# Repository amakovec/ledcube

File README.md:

# blinky++ - An LED cube with some neat features

## Status

**This project has not yet been tested.  Boards are on their way and bring-up FW writing is in-progress.**

## Features

* Multiplex layers at >=120 Hz to create a persistence-of-vision effect
* USB-C for power and communications (except flashing)
    * Set current limit based on CC1 and CC2 voltage (not USB PD)
* Headers to allow for removal of the LED cube
* 30mA per LED
* Buttons to change displayed LED patterns
* Adjustable brightness
    * Limit brightness based on USB current limit determined above

## Hardware

* 2-layer board
* Less than 100x100mm (most budget PCB fabs have a significant price jump for dimensions larger than this)
* SAMD21-based

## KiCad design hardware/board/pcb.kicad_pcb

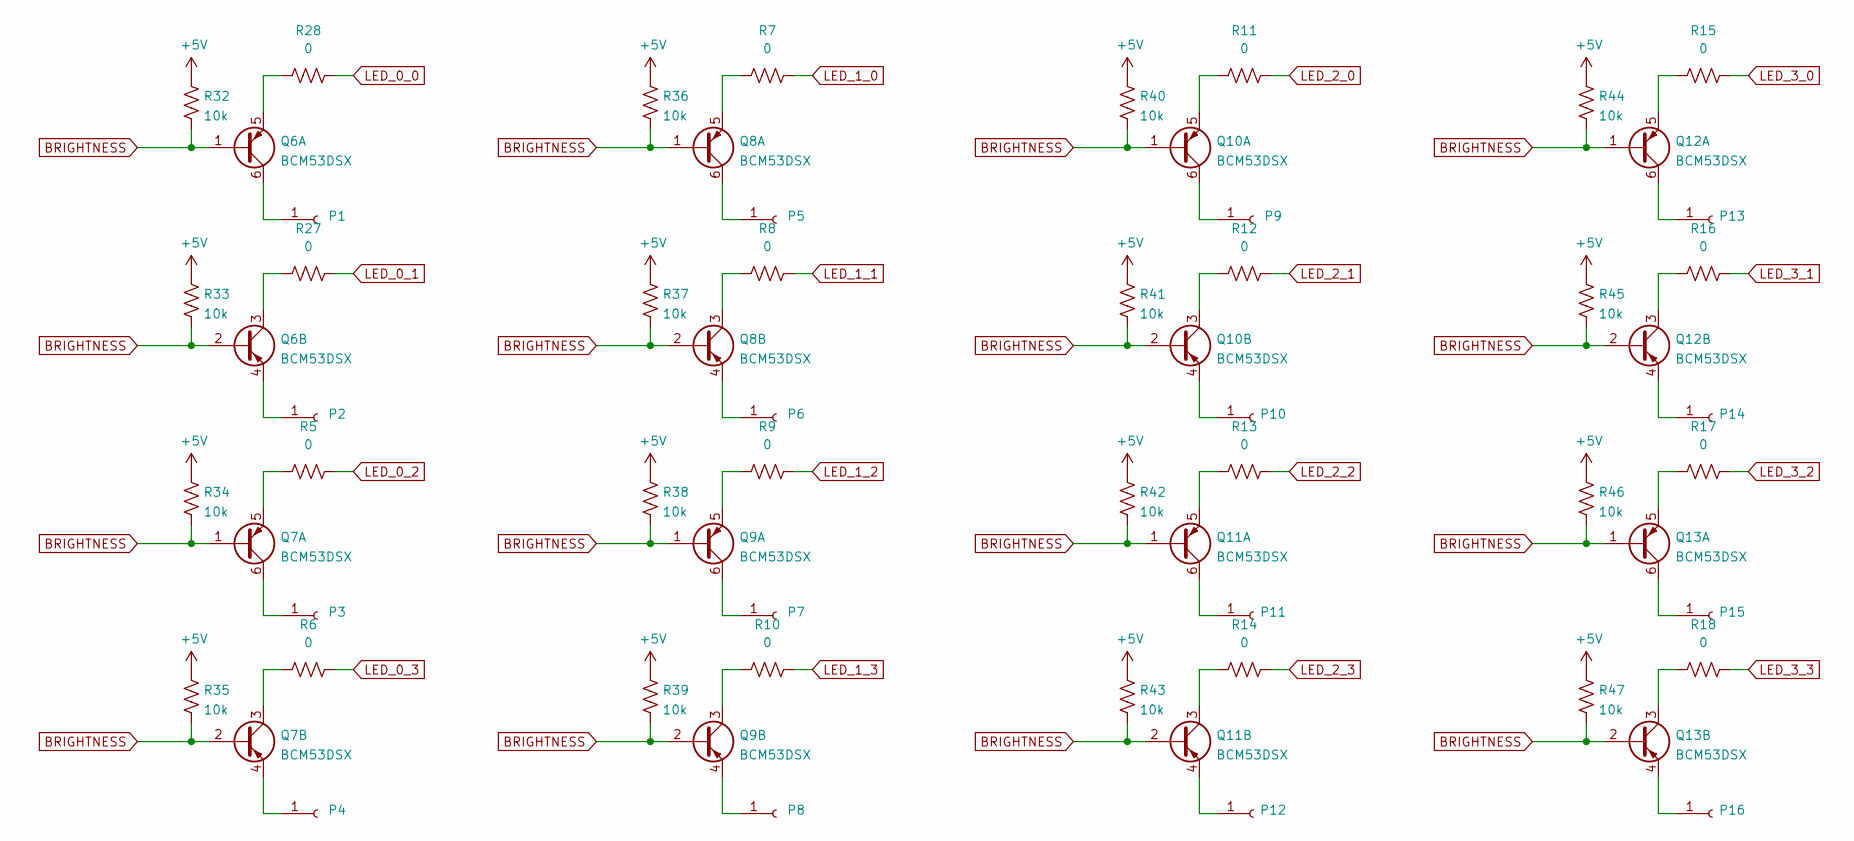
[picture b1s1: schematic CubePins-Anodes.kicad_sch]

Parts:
P1, P2, P3, P4, P5, P6, P7, P8, P9, P10, P11, P12, P13, P14, P15, P16: SSW-101-01-T-S
Q6, Q7, Q8, Q9, Q10, Q11, Q12, Q13: BCM53DSX; SC-74-6_1.5x2.9mm_P0.95mm
R5, R6, R7, R8, R9, R10, R11, R12, R13, R14, R15, R16, R17, R18, R27, R28: RC0402JR-070RP; R_0402_1005Metric_Pad0.72x0.64mm_HandSolder
R32, R33, R34, R35, R36, R37, R38, R39, R40, R41, R42, R43, R44, R45, R46, R47: RC0402FR-0710KL; R_0402_1005Metric_Pad0.72x0.64mm_HandSolder; Tolerance 1%

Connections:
+5V: R32.1, R33.1, R34.1, R35.1, R36.1, R37.1, R38.1, R39.1, R40.1, R41.1, R42.1, R43.1, R44.1, R45.1, R46.1, R47.1; also elsewhere on the board
BRIGHTNESS: Q6.1 (B2), Q6.2 (B2), Q7.1 (B2), Q7.2 (B2), Q8.1 (B2), Q8.2 (B2), Q9.1 (B2), Q9.2 (B2), Q10.1 (B2), Q10.2 (B2), Q11.1 (B2), Q11.2 (B2), Q12.1 (B2), Q12.2 (B2), Q13.1 (B2), Q13.2 (B2), R32.2, R33.2, R34.2, R35.2, R36.2, R37.2, R38.2, R39.2, R40.2, R41.2, R42.2, R43.2, R44.2, R45.2, R46.2, R47.2; also elsewhere on the board
LED_0_0: R28.1; also elsewhere on the board
LED_0_1: R27.1; also elsewhere on the board
LED_0_2: R5.1; also elsewhere on the board
LED_0_3: R6.1; also elsewhere on the board
LED_1_0: R7.1; also elsewhere on the board
LED_1_1: R8.1; also elsewhere on the board
LED_1_2: R9.1; also elsewhere on the board
LED_1_3: R10.1; also elsewhere on the board
LED_2_0: R11.1; also elsewhere on the board
LED_2_1: R12.1; also elsewhere on the board
LED_2_2: R13.1; also elsewhere on the board
LED_2_3: R14.1; also elsewhere on the board
LED_3_0: R15.1; also elsewhere on the board
LED_3_1: R16.1; also elsewhere on the board
LED_3_2: R17.1; also elsewhere on the board
LED_3_3: R18.1; also elsewhere on the board
unnamed: P1.1, Q6.6 (C2)
unnamed: P2.1, Q6.4 (E2)
unnamed: P3.1, Q7.6 (C2)
unnamed: P4.1, Q7.4 (E2)
unnamed: P5.1, Q8.6 (C2)
unnamed: P6.1, Q8.4 (E2)
unnamed: P7.1, Q9.6 (C2)
unnamed: P8.1, Q9.4 (E2)
unnamed: P9.1, Q10.6 (C2)
unnamed: P10.1, Q10.4 (E2)
unnamed: P11.1, Q11.6 (C2)
unnamed: P12.1, Q11.4 (E2)
unnamed: P13.1, Q12.6 (C2)
unnamed: P14.1, Q12.4 (E2)
unnamed: P15.1, Q13.6 (C2)
unnamed: P16.1, Q13.4 (E2)
unnamed: Q6.3 (C2), R27.2
unnamed: Q6.5 (E2), R28.2
unnamed: Q7.3 (C2), R6.2
unnamed: Q7.5 (E2), R5.2
unnamed: Q8.3 (C2), R8.2
unnamed: Q8.5 (E2), R7.2
unnamed: Q9.3 (C2), R10.2
unnamed: Q9.5 (E2), R9.2
unnamed: Q10.3 (C2), R12.2
unnamed: Q10.5 (E2), R11.2
unnamed: Q11.3 (C2), R14.2
unnamed: Q11.5 (E2), R13.2
unnamed: Q12.3 (C2), R16.2
unnamed: Q12.5 (E2), R15.2
unnamed: Q13.3 (C2), R18.2
unnamed: Q13.5 (E2), R17.2

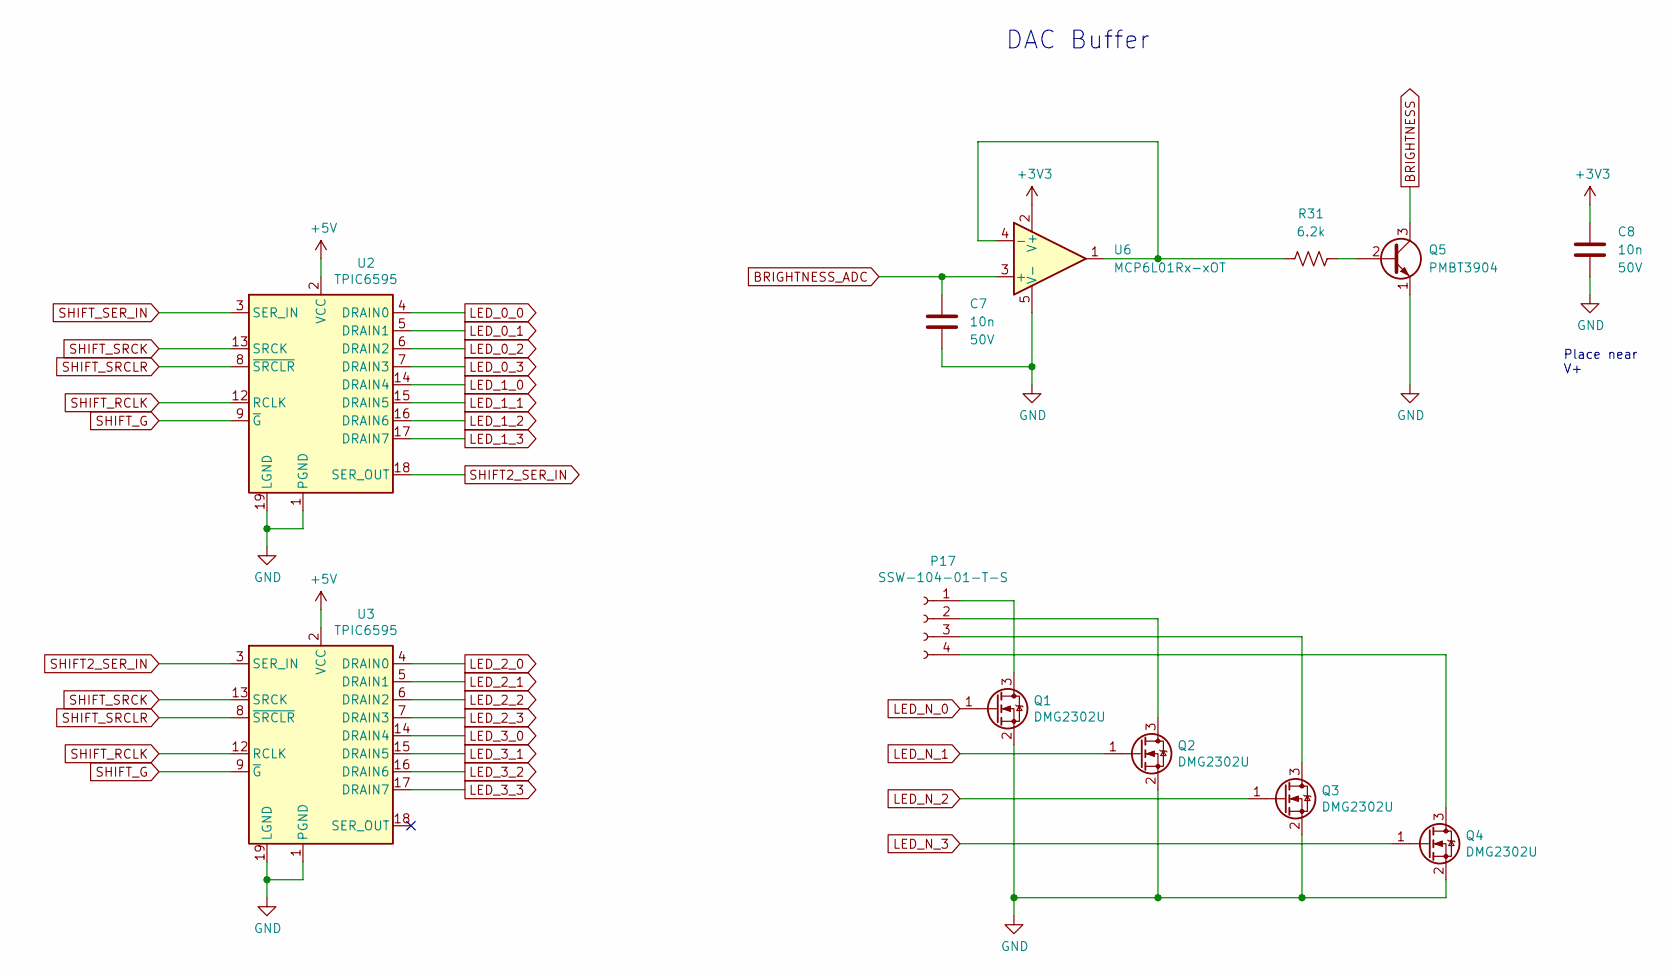
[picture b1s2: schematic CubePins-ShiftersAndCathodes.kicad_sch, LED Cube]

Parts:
C7, C8: GCM155R71H103KA55D; C_0402_1005Metric_Pad0.74x0.62mm_HandSolder; Voltage 50V; Rating X7R
P17: SSW-104-01-T-S
Q1, Q2, Q3, Q4: DMG2302U; SOT-23
Q5: PMBT3904; SOT-23
R31: RC0402FR-076K2L; R_0402_1005Metric_Pad0.72x0.64mm_HandSolder; Tolerance 1%
U2, U3: TPIC6595; SOIC-20W_7.5x12.8mm_P1.27mm
U6: MCP6L01Rx-xOT; SOT-23-5

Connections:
+3V3: C8.1, U6.2 (V+); also elsewhere on the board
+5V: U2.2 (VCC), U3.2 (VCC); also elsewhere on the board
BRIGHTNESS: Q5.3 (C); also elsewhere on the board
BRIGHTNESS_ADC: C7.1, U6.3 (+); also elsewhere on the board
LED_0_0: U2.4 (DRAIN0); also elsewhere on the board
LED_0_1: U2.5 (DRAIN1); also elsewhere on the board
LED_0_2: U2.6 (DRAIN2); also elsewhere on the board
LED_0_3: U2.7 (DRAIN3); also elsewhere on the board
LED_1_0: U2.14 (DRAIN4); also elsewhere on the board
LED_1_1: U2.15 (DRAIN5); also elsewhere on the board
LED_1_2: U2.16 (DRAIN6); also elsewhere on the board
LED_1_3: U2.17 (DRAIN7); also elsewhere on the board
LED_2_0: U3.4 (DRAIN0); also elsewhere on the board
LED_2_1: U3.5 (DRAIN1); also elsewhere on the board
LED_2_2: U3.6 (DRAIN2); also elsewhere on the board
LED_2_3: U3.7 (DRAIN3); also elsewhere on the board
LED_3_0: U3.14 (DRAIN4); also elsewhere on the board
LED_3_1: U3.15 (DRAIN5); also elsewhere on the board
LED_3_2: U3.16 (DRAIN6); also elsewhere on the board
LED_3_3: U3.17 (DRAIN7); also elsewhere on the board
LED_N_0: Q1.1 (G); also elsewhere on the board
LED_N_1: Q2.1 (G); also elsewhere on the board
LED_N_2: Q3.1 (G); also elsewhere on the board
LED_N_3: Q4.1 (G); also elsewhere on the board
unnamed: P17.1, Q1.3 (D)
unnamed: P17.2, Q2.3 (D)
unnamed: P17.3, Q3.3 (D)
unnamed: P17.4, Q4.3 (D)
unnamed: Q5.2 (B), R31.2
unnamed: R31.1, U6.1, U6.4 (-)
SHIFT2_SER_IN: U2.18 (SER_OUT), U3.3 (SER_IN)
SHIFT_G: U2.9 (~G), U3.9 (~G); also elsewhere on the board
SHIFT_RCLK: U2.12 (RCLK), U3.12 (RCLK); also elsewhere on the board
SHIFT_SER_IN: U2.3 (SER_IN); also elsewhere on the board
SHIFT_SRCK: U2.13 (SRCK), U3.13 (SRCK); also elsewhere on the board
SHIFT_SRCLR: U2.8 (~SRCLR), U3.8 (~SRCLR); also elsewhere on the board

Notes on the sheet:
DAC Buffer
Place near V+

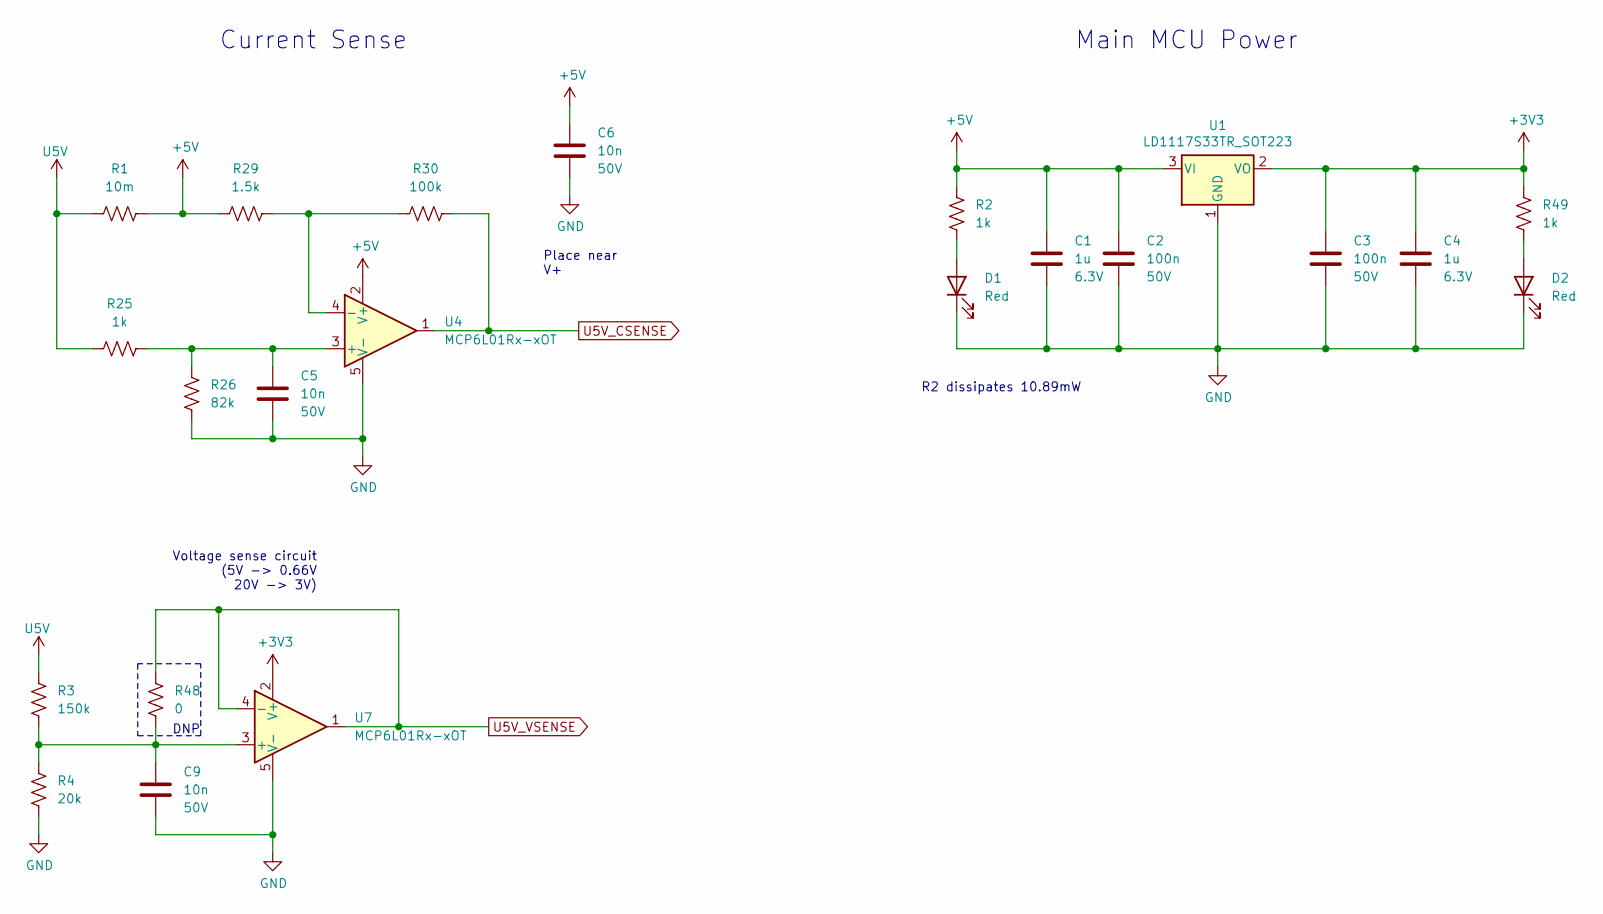
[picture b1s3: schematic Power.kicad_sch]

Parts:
C1, C4: CC0402KRX5R5BB105; C_0402_1005Metric_Pad0.74x0.62mm_HandSolder; Voltage 6.3V; Rating X5R
C2, C3: GRM155R71H104KE14D; C_0402_1005Metric_Pad0.74x0.62mm_HandSolder; Voltage 50V; Rating X7R
C5, C6, C9: GCM155R71H103KA55D; C_0402_1005Metric_Pad0.74x0.62mm_HandSolder; Voltage 50V; Rating X7R
D1, D2: 150060RS75000; LED_0603_1608Metric_Pad1.05x0.95mm_HandSolder
R1: CFG0612-FX-R010ELF; R_1206_3216Metric_Pad1.30x1.75mm_HandSolder; Tolerance 1%
R2, R49: RC0402JR-071KL; R_0402_1005Metric_Pad0.72x0.64mm_HandSolder
R3: RC0402FR-07150KL; R_0402_1005Metric_Pad0.72x0.64mm_HandSolder; Tolerance 1%
R4: RC0402FR-0720KL; R_0402_1005Metric_Pad0.72x0.64mm_HandSolder; Tolerance 1%
R25: RC0402FR-071KL; R_0402_1005Metric_Pad0.72x0.64mm_HandSolder; Tolerance 1%
R26: RC0402FR-0782KL; R_0402_1005Metric_Pad0.72x0.64mm_HandSolder; Tolerance 1%
R29: RC0402FR-071K5L; R_0402_1005Metric_Pad0.72x0.64mm_HandSolder; Tolerance 1%
R30: RC0402FR-07100KL; R_0402_1005Metric_Pad0.72x0.64mm_HandSolder; Tolerance 1%
R48: RC0402JR-070RP; R_0402_1005Metric_Pad0.72x0.64mm_HandSolder
U1: LD1117S33TR_SOT223; SOT-223-3_TabPin2
U4, U7: MCP6L01Rx-xOT; SOT-23-5

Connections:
+3V3: C3.1, C4.1, R49.1, U1.2 (VO), U7.2 (V+); also elsewhere on the board
+5V: C1.1, C2.1, C6.1, R1.2, R2.1, R29.1, U1.3 (VI), U4.2 (V+); also elsewhere on the board
unnamed: C5.1, R25.2, R26.1, U4.3 (+)
unnamed: C9.1, R3.2, R4.1, R48.1, U7.3 (+)
unnamed: D1.2 (A), R2.2
unnamed: D2.2 (A), R49.2
unnamed: R29.2, R30.1, U4.4 (-)
U5V: R1.1, R3.1, R25.1; also elsewhere on the board
U5V_CSENSE: R30.2, U4.1; also elsewhere on the board
U5V_VSENSE: R48.2, U7.1, U7.4 (-); also elsewhere on the board

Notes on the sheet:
DNP
Current Sense
Voltage sense circuit (5V -> 0.66V 20V -> 3V)
Place near V+
R2 dissipates 10.89mW
Main MCU Power

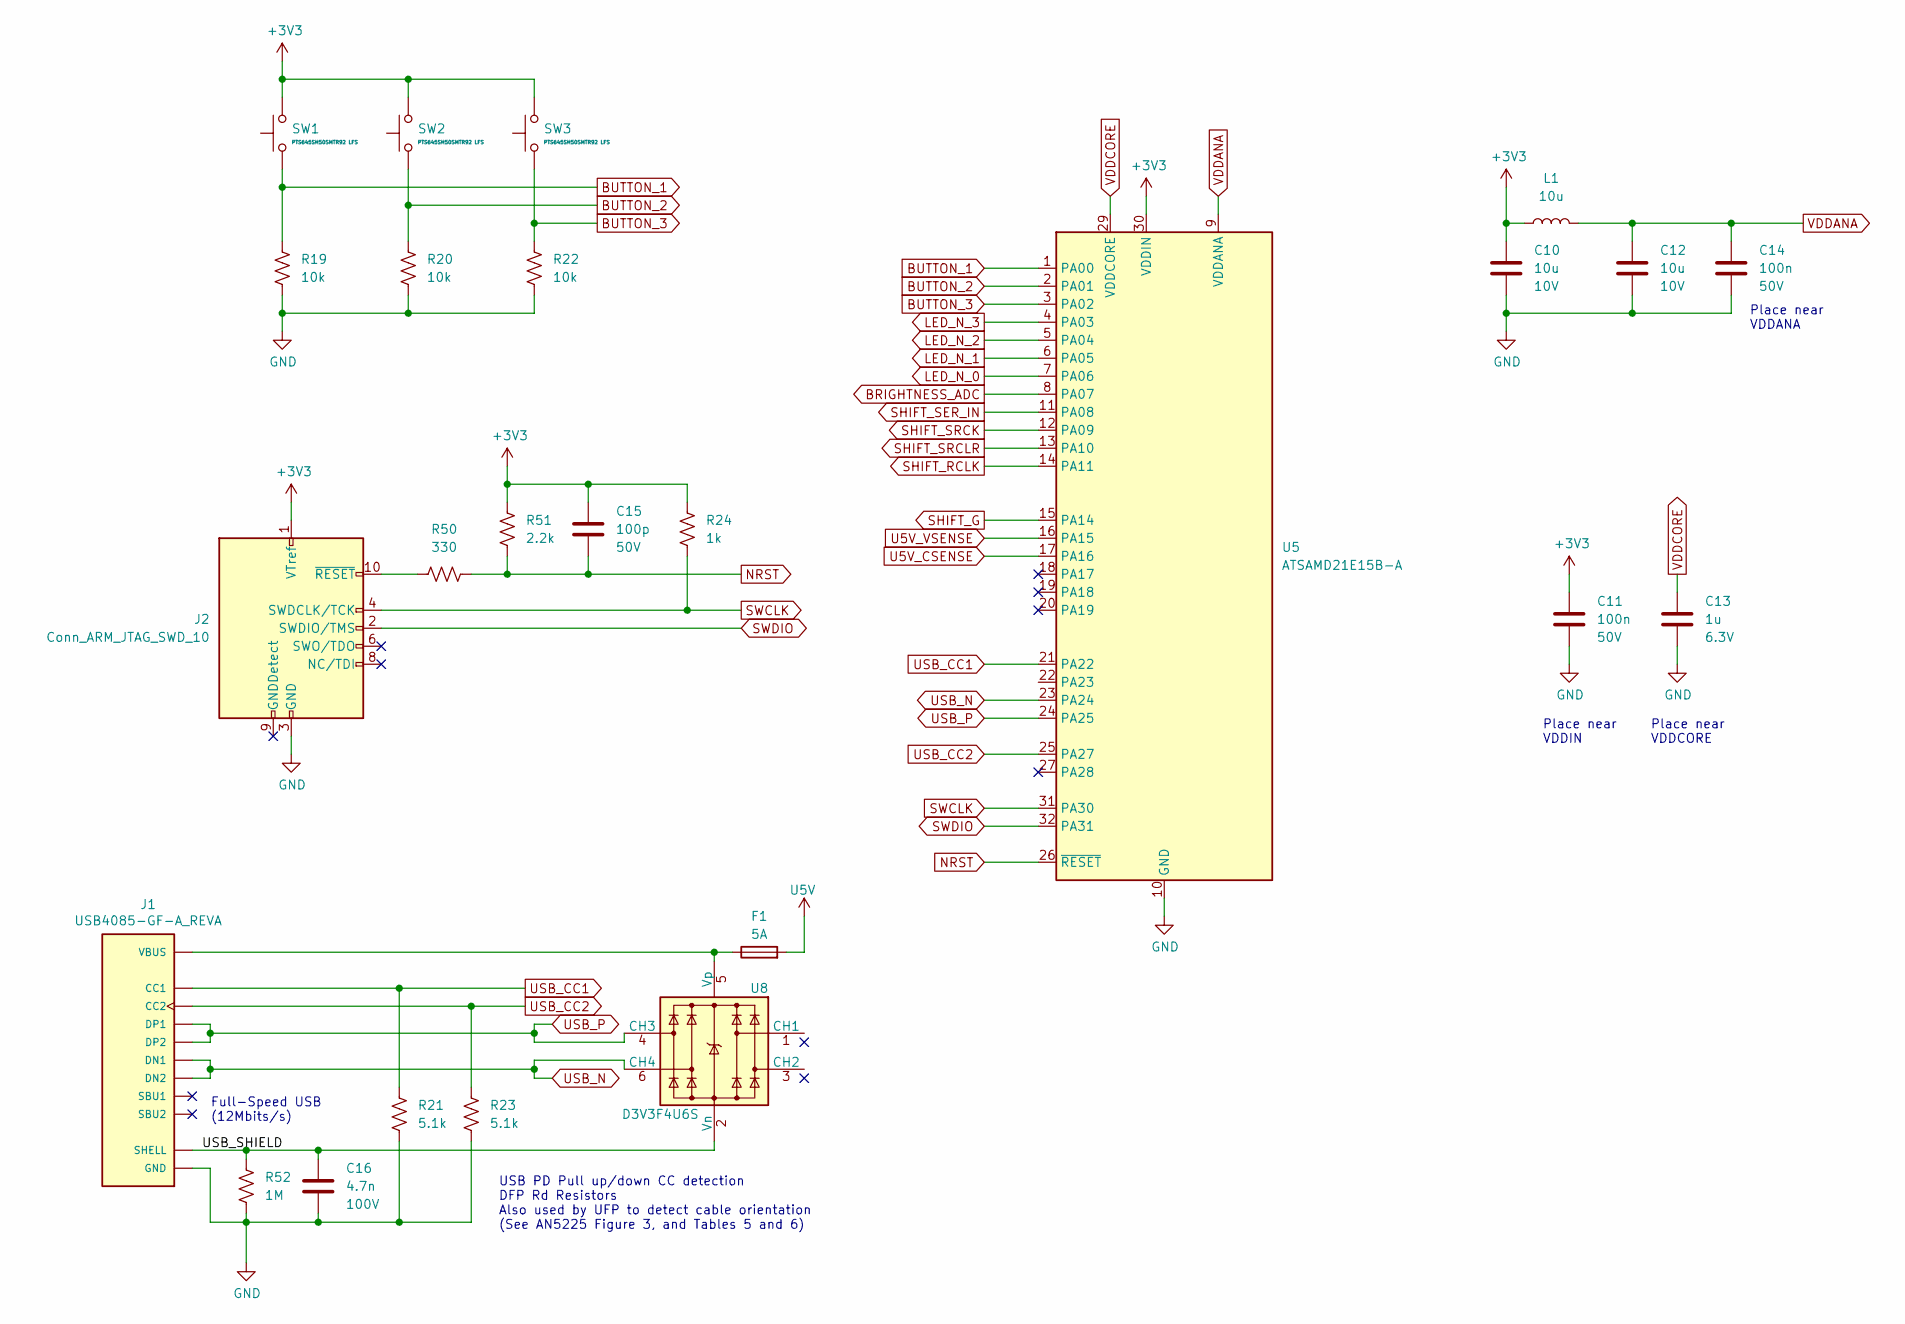
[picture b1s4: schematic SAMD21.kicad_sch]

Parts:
C10, C12: CL21A106KPCLQNC; C_0805_2012Metric_Pad1.18x1.45mm_HandSolder; Voltage 10V; Rating X5R
C11, C14: GRM155R71H104KE14D; C_0402_1005Metric_Pad0.74x0.62mm_HandSolder; Voltage 50V; Rating X7R
C13: CC0402KRX5R5BB105; C_0402_1005Metric_Pad0.74x0.62mm_HandSolder; Voltage 6.3V; Rating X5R
C15: GRM1555C1H101JA01J; C_0402_1005Metric_Pad0.74x0.62mm_HandSolder; Voltage 50V; Rating C0G
C16: GCM155R72A472KA37D; C_0402_1005Metric_Pad0.74x0.62mm_HandSolder; Voltage 100V; Rating X7R
F1: 0685T5000; Fuse_1206_3216Metric_Pad1.42x1.75mm_HandSolder; Current Rating 5A; Voltage Rating - DC 63V
J1: USB4085-GF-A_REVA; GCT_USB4085-GF-A_REVA; PARTREV A2
J2: Conn_ARM_JTAG_SWD_10; TST-105-01-T-D
L1: CBC2518T100M; L_1008_2520Metric_Pad1.43x2.20mm_HandSolder
R19, R20, R22: RC0402JR-0710KL; R_0402_1005Metric_Pad0.72x0.64mm_HandSolder
R21, R23: RC0402FR-075K1L; R_0402_1005Metric_Pad0.72x0.64mm_HandSolder; Tolerance 1%
R24: RC0402JR-071KL; R_0402_1005Metric_Pad0.72x0.64mm_HandSolder
R50: RC0402FR-07330RL; R_0402_1005Metric_Pad0.72x0.64mm_HandSolder; Tolerance 1%
R51: RK73H1ETTP2201F; R_0402_1005Metric_Pad0.72x0.64mm_HandSolder; Tolerance 1%
R52: CRGCQ0402F1M0; R_0402_1005Metric_Pad0.72x0.64mm_HandSolder; Tolerance 1%
SW1, SW2, SW3: PTS645SH50SMTR92 LFS; SW_Push_1P1T_NO_6x6mm_H9.5mm
U5: ATSAMD21E15B-A; TQFP-32_7x7mm_P0.8mm
U8: D3V3F4U6S; SOT-363_SC-70-6

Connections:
+3V3: C10.1, C11.1, C15.1, J2.1 (VTref), L1.1, R24.1, R51.1, SW1.2, SW2.2, SW3.2, U5.30 (VDDIN); also elsewhere on the board
/SAMD21/USB_SHIELD: C16.1, J1.P1 (SHELL), J1.P2 (SHELL), J1.P3 (SHELL), J1.P4 (SHELL), R52.1, U8.2 (Vn)
BRIGHTNESS_ADC: U5.8 (PA07); also elsewhere on the board
BUTTON_1: R19.2, SW1.1, U5.1 (PA00)
BUTTON_2: R20.2, SW2.1, U5.2 (PA01)
BUTTON_3: R22.2, SW3.1, U5.3 (PA02)
LED_N_0: U5.7 (PA06); also elsewhere on the board
LED_N_1: U5.6 (PA05); also elsewhere on the board
LED_N_2: U5.5 (PA04); also elsewhere on the board
LED_N_3: U5.4 (PA03); also elsewhere on the board
NRST: C15.2, R50.2, R51.2, U5.26 (~RESET)
unnamed: F1.1, J1.A4 (VBUS), J1.A9 (VBUS), J1.B4 (VBUS), J1.B9 (VBUS), U8.5 (Vp)
unnamed: J2.10 (~RESET), R50.1
SHIFT_G: U5.15 (PA14); also elsewhere on the board
SHIFT_RCLK: U5.14 (PA11); also elsewhere on the board
SHIFT_SER_IN: U5.11 (PA08); also elsewhere on the board
SHIFT_SRCK: U5.12 (PA09); also elsewhere on the board
SHIFT_SRCLR: U5.13 (PA10); also elsewhere on the board
SWCLK: J2.4 (SWDCLK/TCK), R24.2, U5.31 (PA30)
SWDIO: J2.2 (SWDIO/TMS), U5.32 (PA31)
U5V: F1.2; also elsewhere on the board
U5V_CSENSE: U5.17 (PA16); also elsewhere on the board
U5V_VSENSE: U5.16 (PA15); also elsewhere on the board
USB_CC1: J1.A5 (CC1), R21.1, U5.21 (PA22)
USB_CC2: J1.B5 (CC2), R23.1, U5.25 (PA27)
USB_N: J1.A7 (DN1), J1.B7 (DN2), U5.23 (PA24), U8.6 (CH4)
USB_P: J1.A6 (DP1), J1.B6 (DP2), U5.24 (PA25), U8.4 (CH3)
VDDANA: C12.1, C14.1, L1.2, U5.9 (VDDANA)
VDDCORE: C13.1, U5.29 (VDDCORE)

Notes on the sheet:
Full-Speed USB (12Mbits/s)
USB PD Pull up/down CC detection DFP Rd Resistors Also used by UFP to detect cable orientation (See AN5225 Figure 3, and Tables 5 and 6)
Place near VDDIN
Place near VDDCORE
Place near VDDANA

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
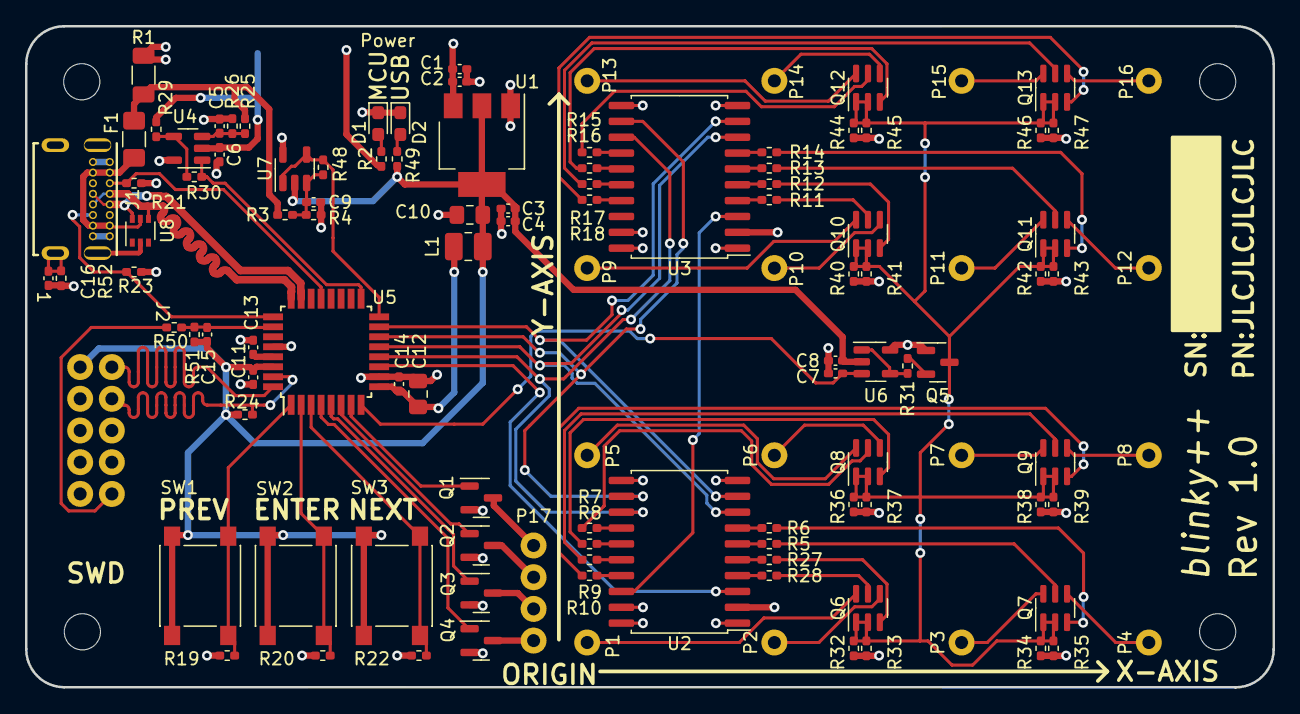
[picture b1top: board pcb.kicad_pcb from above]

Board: 2 copper layers, 100.0 x 53.0 mm, 119 parts (0 on the bottom side), 92 nets.

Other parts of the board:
REF1, REF2, REF3, REF4: HEX_STANDOFF_4-40_NYLON_0.5in

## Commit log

2021-09-13 feat: Initial commit with Rev 1.0 files
